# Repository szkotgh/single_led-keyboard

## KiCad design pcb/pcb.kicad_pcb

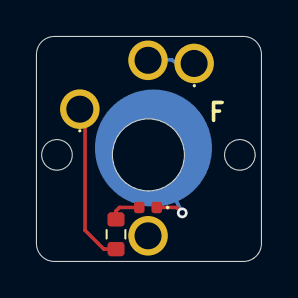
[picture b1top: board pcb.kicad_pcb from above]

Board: 2 copper layers, 12.5 x 12.5 mm, 3 parts (0 on the bottom side), 2 nets.

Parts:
D1: BLUE; LED_0402_1005Metric
R1: 47; R_0603_1608Metric
SW1: KEY_SW; SW_Cherry_MX_1.00u_PCB

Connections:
unnamed: D1.2 (A), R1.1
unnamed: R1.2, SW1.2

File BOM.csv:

"Reference","Value","Datasheet","Footprint","Qty","DNP"
"B1","3V","","Battery:BatteryHolder_LINX_BAT-HLD-012-SMT","1",""
"D1","BLUE","~","LED_SMD:LED_0402_1005Metric","1",""
"R1","47","~","LED_SMD:LED_0201_0603Metric","1",""
"SW1","KEY_SW","~","Button_Switch_Keyboard:SW_Cherry_MX_1.00u_PCB","1",""

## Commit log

2024-10-24 update: pcb folder added
2024-10-24 update: README.md created
2024-10-24 update: LICENSE created
2024-11-12 update: last updated
2024-11-15 update: pcb update
2025-05-09 update: update
2025-06-18 update: bia update
